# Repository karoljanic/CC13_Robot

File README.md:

# CC13_Robot
This is a robot project modeled on BB8. 
The construction is modelled in Autodesk Fusion 360 and printed using 3D printing technology. I currently use Creality Ender 3. 
The electronics is based on the STM21F1038C and self-made PCB / Arduino Nano 33 BLE Sense processor. 
The robot is controlled by a mobile app via Bluetooth. It is developed in Android Studio. 
Work still in progress.

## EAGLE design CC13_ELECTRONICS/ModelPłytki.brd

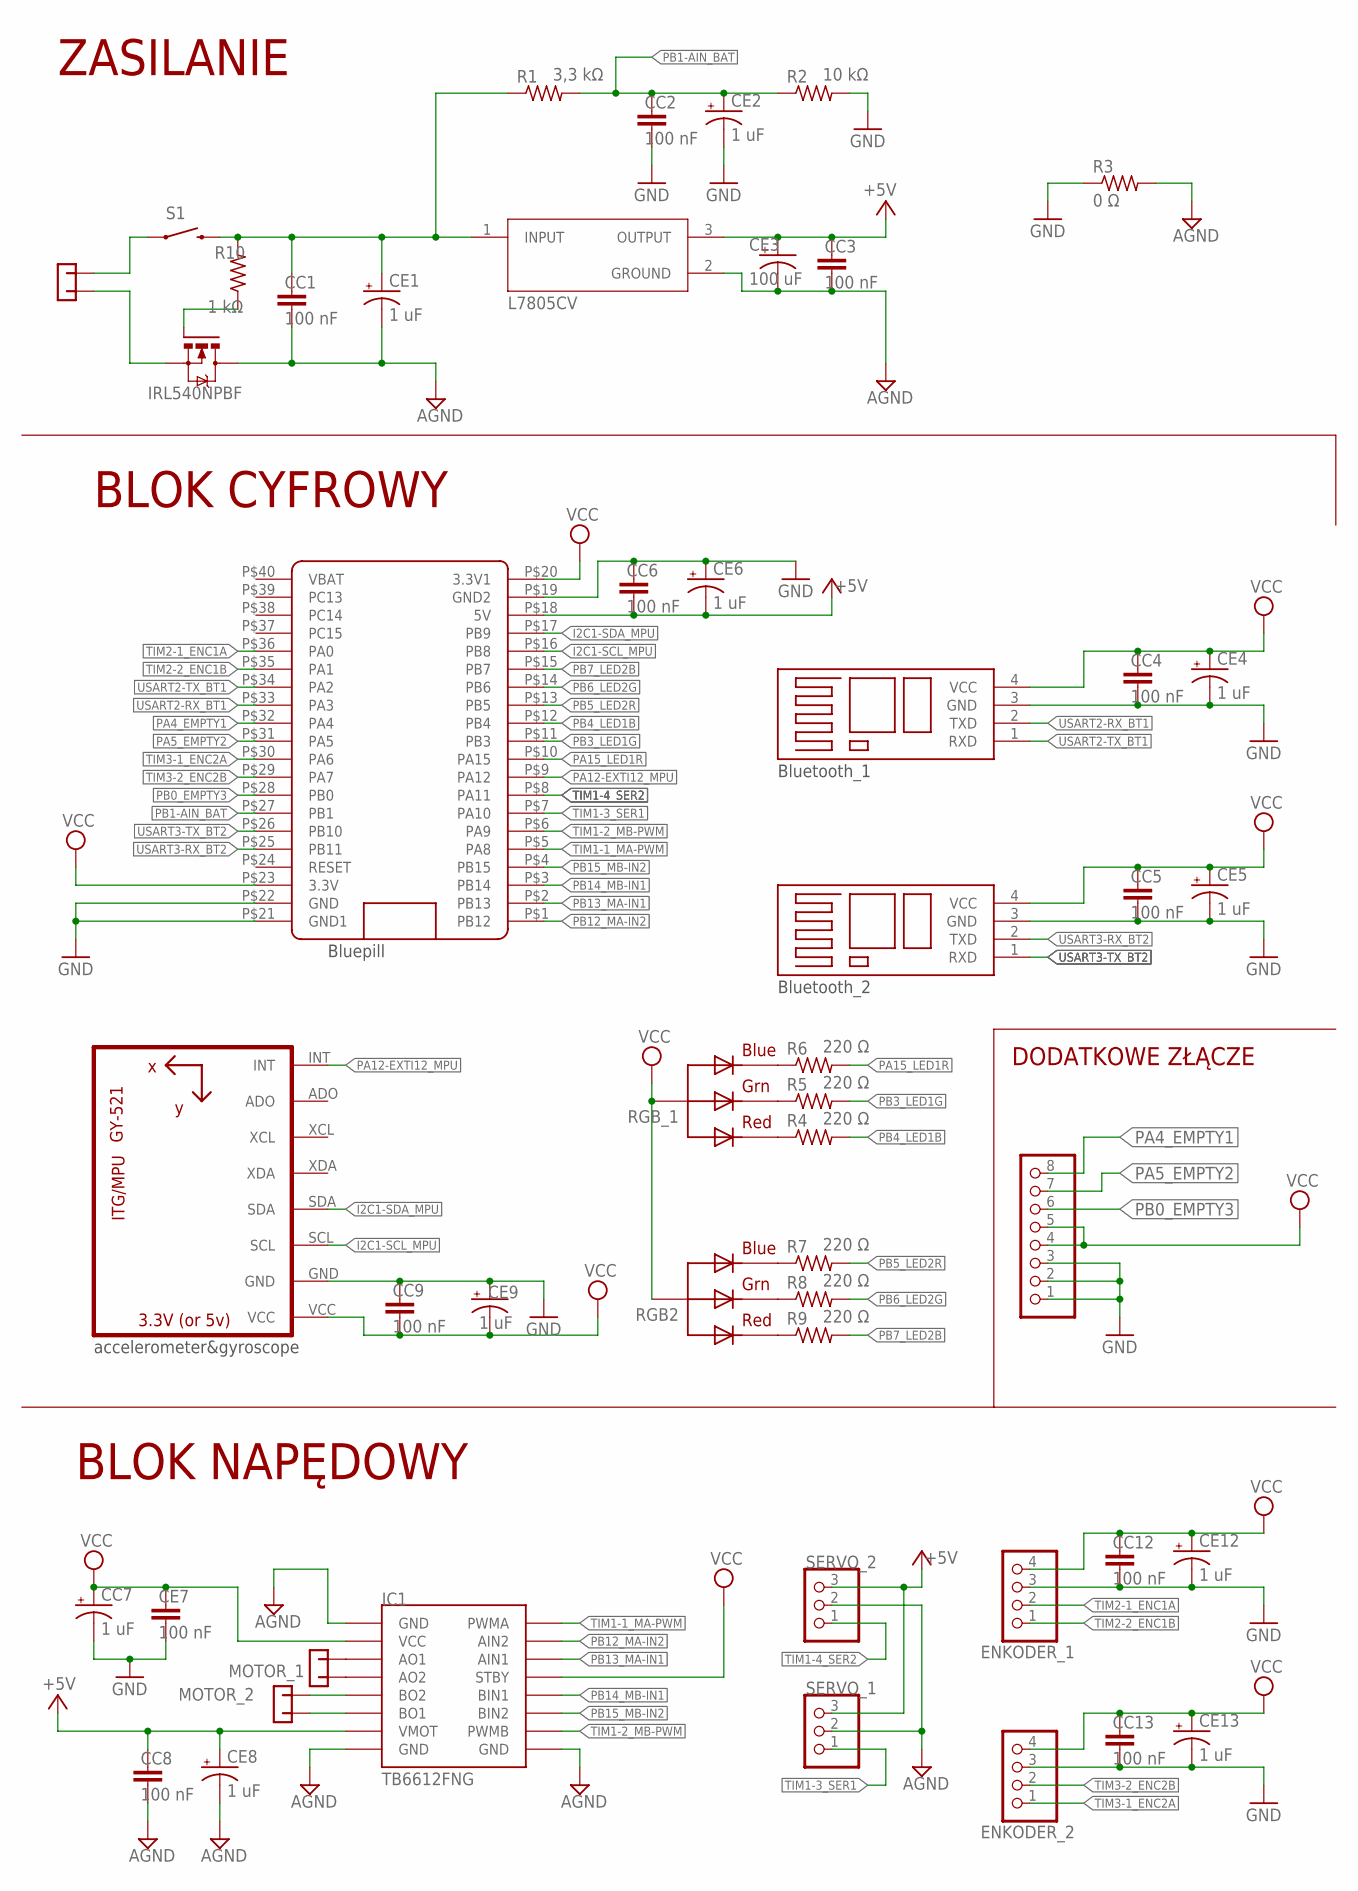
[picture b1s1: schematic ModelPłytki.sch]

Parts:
BATERIA: -CON2; CON2
BLUETOOTH2, BLUETOOTH3: BLUETOOTH
CC1, CC2, CC3, CC4, CC5, CC6, CC8, CC9, CC12, CC13: 100 nF; C025-030X050
CC7: 1 uF; TT2D5
CE1, CE2, CE4, CE5, CE6, CE8, CE9, CE12, CE13: 1 uF; TT2D5
CE3: 100 uF; TT2D5
CE7: 100 nF; C025-030X050
ENKODER_1, ENKODER_2: PINHD-1X4; 1X04
IC1: MODUL_POLOLU
IRL540NPBF: IRF520; TO220BV
JP4: PINHD-1X8BIG; 1X08-BIG
MOTOR_1, MOTOR_2: -CON2; CON2
R1: 3,3 kΩ; 0309/12
R2: 10 kΩ; 0309/12
R3: 0 Ω; 0309/12
R4, R5, R6, R7, R8, R9: 220 Ω; 0309/12
R10: 1 kΩ; 0309/12
RGB2: RGBLED_CA-5MM; LED5MMRGB
RGB_1: RGBLED_CA-5MM; LED5MMRGB
S1: RS032G05A3SM-SPST-MOMENTARY-SWSMD-1101NE; TACTILE-SWITCH-1101NE
SERVO_1, SERVO_2: PINHD-1X3; 1X03
U2: L7805CV; TO255P1040X460X1968-3
U4: GY-521MPU6050; GY-521
U$2: BLUE_PILL

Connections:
+5V: CC3.1, CC6.2, CC8.1, CE3.+, CE6.-, CE8.+, IC1.VMOT, SERVO_1.3, SERVO_2.3, U2.3 (OUTPUT), U$2.P$18 (5V)
AGND: CC1.2, CC3.2, CC8.2, CE1.-, CE3.-, CE8.-, IC1.GND1 (GND), IC1.GND2 (GND), IC1.GND3 (GND), IRL540NPBF.D, R3.2, SERVO_1.2, SERVO_2.2, U2.2 (GROUND)
GND: BLUETOOTH2.3 (GND), BLUETOOTH3.3 (GND), CC2.2, CC4.2, CC5.2, CC6.1, CC7.-, CC9.1, CC12.2, CC13.2, CE2.-, CE4.-, CE5.-, CE6.+, CE7.2, CE9.+, CE12.-, CE13.-, ENKODER_1.3, ENKODER_2.3, JP4.1, JP4.2, JP4.3, R2.2, R3.1, U4.GND, U$2.P$19 (GND2), U$2.P$21 (GND1), U$2.P$22 (GND)
I2C1-SCL_MPU: U4.SCL, U$2.P$16 (PB8)
I2C1-SDA_MPU: U4.SDA, U$2.P$17 (PB9)
unnamed: IRL540NPBF.G, R10.1
unnamed: IC1.BO2, MOTOR_2.P$1 (1)
unnamed: IC1.A02 (AO2), MOTOR_1.P$2 (2)
unnamed: IC1.BO1, MOTOR_2.P$2 (2)
unnamed: BATERIA.P$1 (1), S1.1
unnamed: R6.1, RGB_1.4 (BLUE)
unnamed: R5.1, RGB_1.3 (GREEN)
unnamed: R4.1, RGB_1.1 (RED)
unnamed: R8.1, RGB2.3 (GREEN)
unnamed: R7.1, RGB2.4 (BLUE)
unnamed: R9.1, RGB2.1 (RED)
unnamed: BATERIA.P$2 (2), IRL540NPBF.S
unnamed: IC1.AO1, MOTOR_1.P$1 (1)
unnamed: CC1.1, CE1.+, R1.1, R10.2, S1.2, U2.1 (INPUT)
PA4_EMPTY1: JP4.8, U$2.P$32 (PA4)
PA5_EMPTY2: JP4.7, U$2.P$31 (PA5)
PA12-EXTI12_MPU: U4.INT, U$2.P$9 (PA12)
PA15_LED1R: R6.2, U$2.P$10 (PA15)
PB0_EMPTY3: JP4.6, U$2.P$28 (PB0)
PB1-AIN_BAT: CC2.1, CE2.+, R1.2, R2.1, U$2.P$27 (PB1)
PB3_LED1G: R5.2, U$2.P$11 (PB3)
PB4_LED1B: R4.2, U$2.P$12 (PB4)
PB5_LED2R: R7.2, U$2.P$13 (PB5)
PB6_LED2G: R8.2, U$2.P$14 (PB6)
PB7_LED2B: R9.2, U$2.P$15 (PB7)
PB12_MA-IN2: IC1.AIN2, U$2.P$1 (PB12)
PB13_MA-IN1: IC1.AIN1, U$2.P$2 (PB13)
PB14_MB-IN1: IC1.BIN1, U$2.P$3 (PB14)
PB15_MB-IN2: IC1.BIN2, U$2.P$4 (PB15)
TIM1-1_MA-PWM: IC1.PWMA, U$2.P$5 (PA8)
TIM1-2_MB-PWM: IC1.PWMB, U$2.P$6 (PA9)
TIM1-3_SER1: SERVO_1.1, U$2.P$7 (PA10)
TIM1-4_SER2: SERVO_2.1, U$2.P$8 (PA11)
TIM2-1_ENC1A: ENKODER_1.2, U$2.P$36 (PA0)
TIM2-2_ENC1B: ENKODER_1.1, U$2.P$35 (PA1)
TIM3-1_ENC2A: ENKODER_2.1, U$2.P$30 (PA6)
TIM3-2_ENC2B: ENKODER_2.2, U$2.P$29 (PA7)
USART2-RX_BT1: BLUETOOTH2.2 (TXD), U$2.P$33 (PA3)
USART2-TX_BT1: BLUETOOTH2.1 (RXD), U$2.P$34 (PA2)
USART3-RX_BT2: BLUETOOTH3.2 (TXD), U$2.P$25 (PB11)
USART3-TX_BT2: BLUETOOTH3.1 (RXD), U$2.P$26 (PB10)
VCC: BLUETOOTH2.4 (VCC), BLUETOOTH3.4 (VCC), CC4.1, CC5.1, CC7.+, CC9.2, CC12.1, CC13.1, CE4.+, CE5.+, CE7.1, CE9.-, CE12.+, CE13.+, ENKODER_1.4, ENKODER_2.4, IC1.STBY, IC1.VCC, JP4.4, JP4.5, RGB2.2 (VCC), RGB_1.2 (VCC), U4.VCC, U$2.P$20 (3.3V1), U$2.P$23 (3.3V)

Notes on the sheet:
ZASILANIE
BLOK CYFROWY
BLOK NAPĘDOWY
Bluetooth_1
Bluetooth_2
Bluepill
accelerometer&gyroscope
DODATKOWE ZŁĄCZE

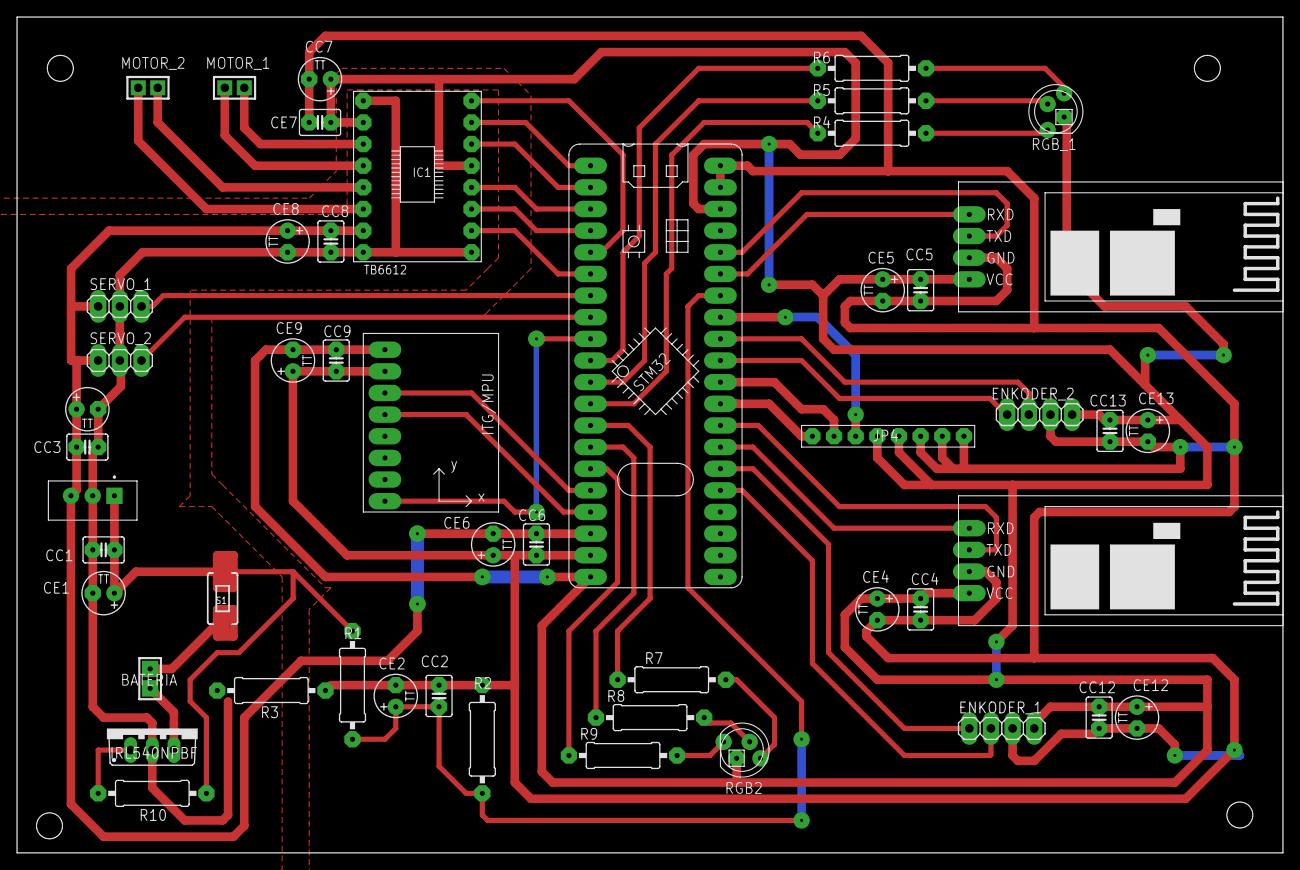
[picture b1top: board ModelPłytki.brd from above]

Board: 2 copper layers, 148.6 x 98.1 mm, 50 parts (0 on the bottom side), 47 nets.

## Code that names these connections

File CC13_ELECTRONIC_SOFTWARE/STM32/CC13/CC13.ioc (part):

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Mcu.Name=STM32F103C(8-B)Tx
Mcu.Package=LQFP48
Mcu.UserName=STM32F103C8Tx
PA0-WKUP.GPIOParameters=GPIO_Label
PA0-WKUP.GPIO_Label=TIM2-1_ENC1A
PA0-WKUP.Signal=S_TIM2_CH1_ETR
PA1.GPIOParameters=GPIO_Label
PA1.GPIO_Label=TIM2-2_ENC1B
PA1.Signal=S_TIM2_CH2
PA10.GPIOParameters=GPIO_Label
PA10.GPIO_Label=TIM1-3_SER1
PA10.Signal=S_TIM1_CH3
PA11.GPIOParameters=GPIO_Label
PA11.GPIO_Label=TIM1-4_SER2
PA11.Signal=S_TIM1_CH4
PA12.GPIOParameters=GPIO_Label
PA12.GPIO_Label=PA12-EXTI12_MPU
PA12.Signal=GPXTI12
PA13.Mode=Serial_Wire
PA13.Signal=SYS_JTMS-SWDIO
PA14.Mode=Serial_Wire
PA14.Signal=SYS_JTCK-SWCLK
PA15.GPIOParameters=GPIO_Label
PA15.GPIO_Label=PA15_LED1R
PA15.Signal=GPIO_Output
PA2.GPIOParameters=GPIO_Label
PA2.GPIO_Label=USART2-TX_BT1
PA2.Mode=Asynchronous
PA2.Signal=USART2_TX
PA3.GPIOParameters=GPIO_Label
PA3.GPIO_Label=USART2-RX_BT1
PA3.Mode=Asynchronous
PA3.Signal=USART2_RX
PA4.Signal=ADCx_IN4
PA5.Signal=ADCx_IN5
PA6.GPIOParameters=GPIO_Label
PA6.GPIO_Label=TIM3-1_ENC2A
PA6.Signal=S_TIM3_CH1
PA7.GPIOParameters=GPIO_Label
PA7.GPIO_Label=TIM3-2_ENC2B
PA7.Signal=S_TIM3_CH2
PA8.GPIOParameters=GPIO_Label
PA8.GPIO_Label=TIM1-1_MA-PWM
PA8.Signal=S_TIM1_CH1
PA9.GPIOParameters=GPIO_Label
PA9.GPIO_Label=TIM1-2_MB-PWM
PA9.Signal=S_TIM1_CH2
PB0.GPIOParameters=GPIO_Label
PB0.GPIO_Label=PB1-AN_5.0V
PB0.Signal=ADCx_IN8
PB1.GPIOParameters=GPIO_Label
PB1.GPIO_Label=PB1-AN_3.3V
PB1.Signal=ADCx_IN9
PB10.GPIOParameters=GPIO_Label
PB10.GPIO_Label=USART3-TX_BT2
PB10.Mode=Asynchronous
PB10.Signal=USART3_TX
PB11.GPIOParameters=GPIO_Label
PB11.GPIO_Label=USART3-RX_BT2
PB11.Mode=Asynchronous
PB11.Signal=USART3_RX
PB12.GPIOParameters=GPIO_Label
PB12.GPIO_Label=PB12_MA-IN2
PB12.Signal=GPIO_Output
PB13.GPIOParameters=GPIO_Label
PB13.GPIO_Label=PB13_MA-IN1
PB13.Signal=GPIO_Output
PB14.GPIOParameters=GPIO_Label
PB14.GPIO_Label=PB14_MB-IN1
PB14.Signal=GPIO_Output
PB15.GPIOParameters=GPIO_Label
PB15.GPIO_Label=PB15_MB-IN2
PB15.Signal=GPIO_Output
PB3.GPIOParameters=GPIO_Label
PB3.GPIO_Label=PB3_LED1G
PB3.Signal=GPIO_Output
PB4.GPIOParameters=GPIO_Label
PB4.GPIO_Label=PB4_LED1B
PB4.Signal=GPIO_Output
PB5.GPIOParameters=GPIO_Label
PB5.GPIO_Label=PB5_LED2R
PB5.Signal=GPIO_Output
PB6.GPIOParameters=GPIO_Label
PB6.GPIO_Label=PB6_LED2G
PB6.Signal=GPIO_Output
PB7.GPIOParameters=GPIO_Label
PB7.GPIO_Label=PB7_LED2B
PB7.Signal=GPIO_Output
PB8.GPIOParameters=GPIO_Label
PB8.GPIO_Label=I2C1-SCL_MPU
PB8.Mode=I2C
PB8.Signal=I2C1_SCL
PB9.GPIOParameters=GPIO_Label
PB9.GPIO_Label=I2C1-SDA_MPU
PB9.Mode=I2C
PB9.Signal=I2C1_SDA
PC13-TAMPER-RTC.Signal=GPIO_Output
PD0-OSC_IN.Mode=HSE-External-Oscillator
PD0-OSC_IN.Signal=RCC_OSC_IN
PD1-OSC_OUT.Mode=HSE-External-Oscillator
PD1-OSC_OUT.Signal=RCC_OSC_OUT
RCC.SYSCLKFreq_VALUE=72000000
RCC.SYSCLKSource=RCC_SYSCLKSOURCE_PLLCLK
board=custom

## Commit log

2020-04-08 add read.me
2021-05-23 Add folders
2021-05-23 New mechanical models
